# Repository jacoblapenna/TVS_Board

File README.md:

### CM4 with MCC 152 hot-plugging active digital sensors

This board was specifically developed for hot-plugging active digital sensors (e.g., a rotary encoder or a laser photoelectric sensor) into the [MCC-152 DAQ HAT](https://digilent.com/shop/mcc-152-voltage-output-and-dio-daq-hat-for-raspberry-pi/) mounted to the [Raspberry Pi I/O board](https://www.raspberrypi.com/products/compute-module-4-io-board/) for the [Raspberry Pi CM4 computer](https://www.raspberrypi.com/products/compute-module-4/?variant=raspberry-pi-cm4001000). The TVS diode array used is a [Semtech SRDA70-4](https://www.digikey.com/en/products/detail/semtech-corporation/SRDA70-4-TBT/5113686). This diode array is a "rail-to-rail" type device and the clamping voltage is set by the reference supplied and the diode forward bias voltage. For this application, the diode is referenced to 3.3 V. Note that this will put transients on the 3.3 V reference source. For this reason, it is important not to connect this reference to the CM4 3.3 V GPIO pin (I tried this first, and the transients caused the CM4 to reboot on every sensor hot-pugging event). I am now pulling the 3.3 V reference from the dedicated input to 3.3 V DC-DC converter on the RPi I/O board. Note that this converter is for the PCIe connection. I am not using PCIe for this application, so am pulling the 3.3 V power from here. I plan to develop my own I/O board with this dedicated 3.3 V trace without the other PCIe traces in the near future. For now, in my prototyping phase, pulling from any of the several 3.3 V wires from a PCIe extender cable is sufficient. This is a dedicated 3.3 V branch from the input power, and so will not affect the CM4's 3.3 V power circuit.

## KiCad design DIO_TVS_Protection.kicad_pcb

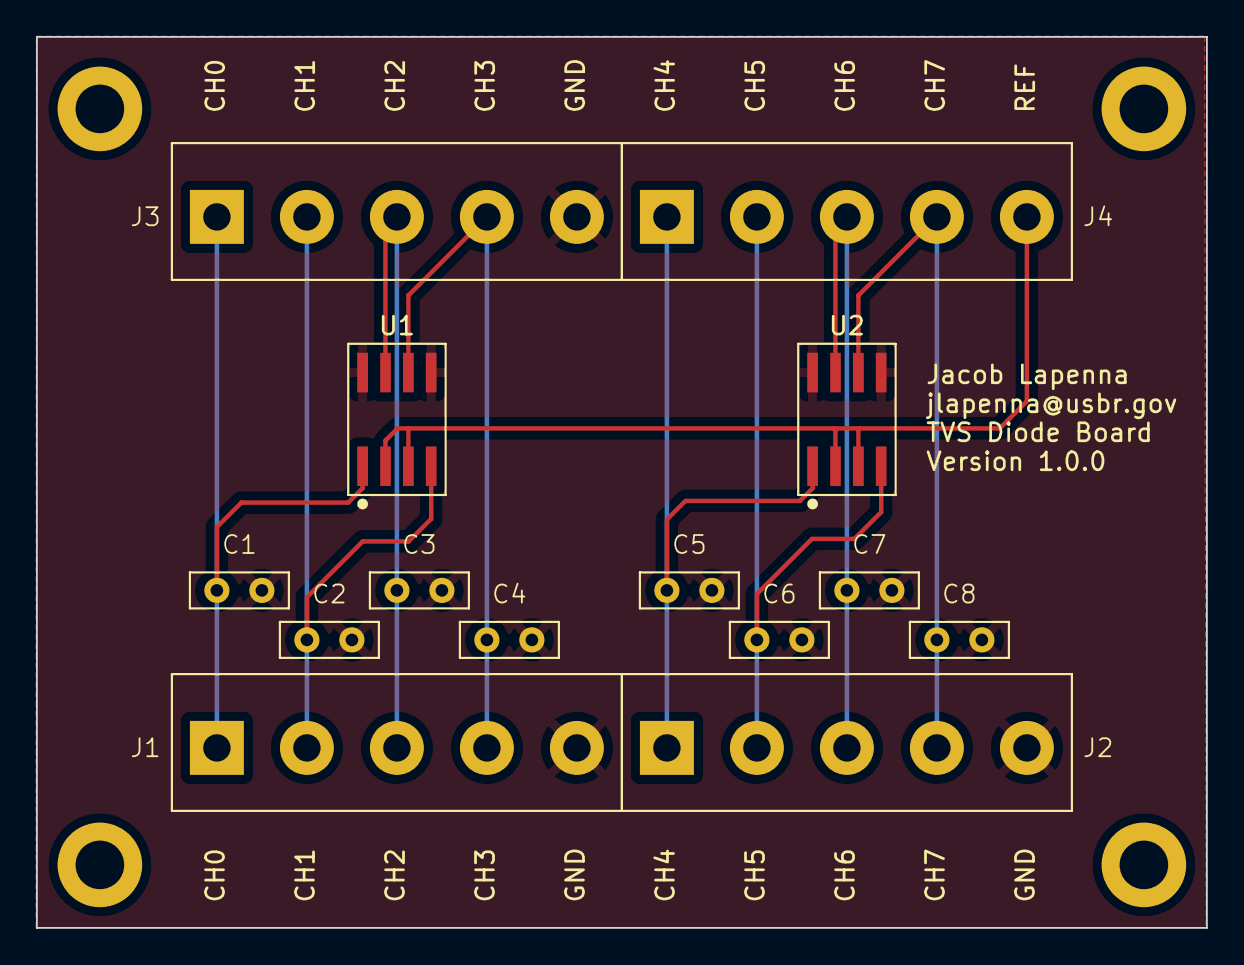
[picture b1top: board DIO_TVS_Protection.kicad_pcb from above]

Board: 2 copper layers, 65.0 x 49.5 mm, 14 parts (0 on the bottom side), 10 nets.

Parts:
C1, C2, C3, C4, C5, C6, C7, C8: C; Bypass_C
J1, J2, J3, J4: Screw_Terminal_01x05; TB002-500
U1, U2: SRDA70-4

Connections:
GND: C1.2, C2.2, C3.2, C4.2, C5.2, C6.2, C7.2, C8.2, J1.5, J2.5, J3.5, U1.5 (GND), U1.8 (GND), U2.5 (GND), U2.8 (GND)
unnamed: C1.1, J1.1, J3.1, U1.1 (Line-0)
unnamed: C2.1, J1.2, J3.2, U1.4 (Line-1)
unnamed: C3.1, J1.3, J3.3, U1.7 (Line-2)
unnamed: C4.1, J1.4, J3.4, U1.6 (Line-3)
unnamed: C5.1, J2.1, J4.1, U2.1 (Line-0)
unnamed: C6.1, J2.2, J4.2, U2.4 (Line-1)
unnamed: C7.1, J2.3, J4.3, U2.7 (Line-2)
unnamed: C8.1, J2.4, J4.4, U2.6 (Line-3)
unnamed: J4.5, U1.2 (Ref), U1.3 (Ref), U2.2 (Ref), U2.3 (Ref)

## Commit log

2024-03-25 Initial commit and push to public.
